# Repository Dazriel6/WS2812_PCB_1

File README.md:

## WS2812 PCB FOR PROTOTYPING
### PCB for WS2812 SMD LED FOR USE IN PROTOBOARD

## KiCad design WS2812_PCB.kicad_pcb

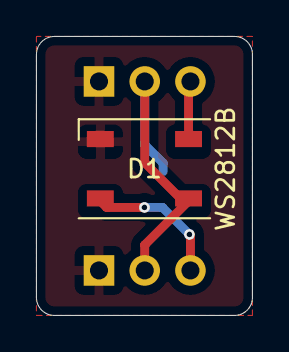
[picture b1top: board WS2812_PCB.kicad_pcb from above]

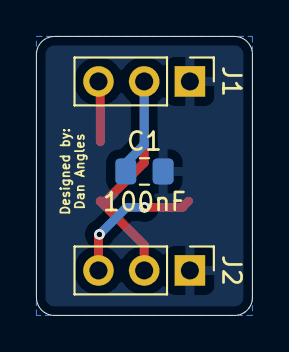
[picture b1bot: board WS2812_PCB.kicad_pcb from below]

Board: 2 copper layers, 12.0 x 15.5 mm, 4 parts (3 on the bottom side), 4 nets.

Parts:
C1: 100nF; C_0805_2012Metric_Pad1.18x1.45mm_HandSolder
D1: WS2812B; LED_WS2812B_PLCC4_5.0x5.0mm_P3.2mm
J1: OUT; PinHeader_1x03_P2.54mm_Vertical
J2: IN; PinHeader_1x03_P2.54mm_Vertical

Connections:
5V: C1.1, D1.1 (VDD), J1.2, J2.2
DIN: D1.4 (DIN), J2.3
DOUT: D1.2 (DOUT), J1.3
GND: C1.2, D1.3 (VSS), J1.1, J2.1

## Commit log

2024-05-28 Primer commit, proyecto finalizado versión 1.0
2024-05-29 Se modifican los archivos de la pcb y esquematico para generar los archivos pdf
2024-05-29 Create README.md
    Readme añadido
2024-05-29 Update README.md added images
